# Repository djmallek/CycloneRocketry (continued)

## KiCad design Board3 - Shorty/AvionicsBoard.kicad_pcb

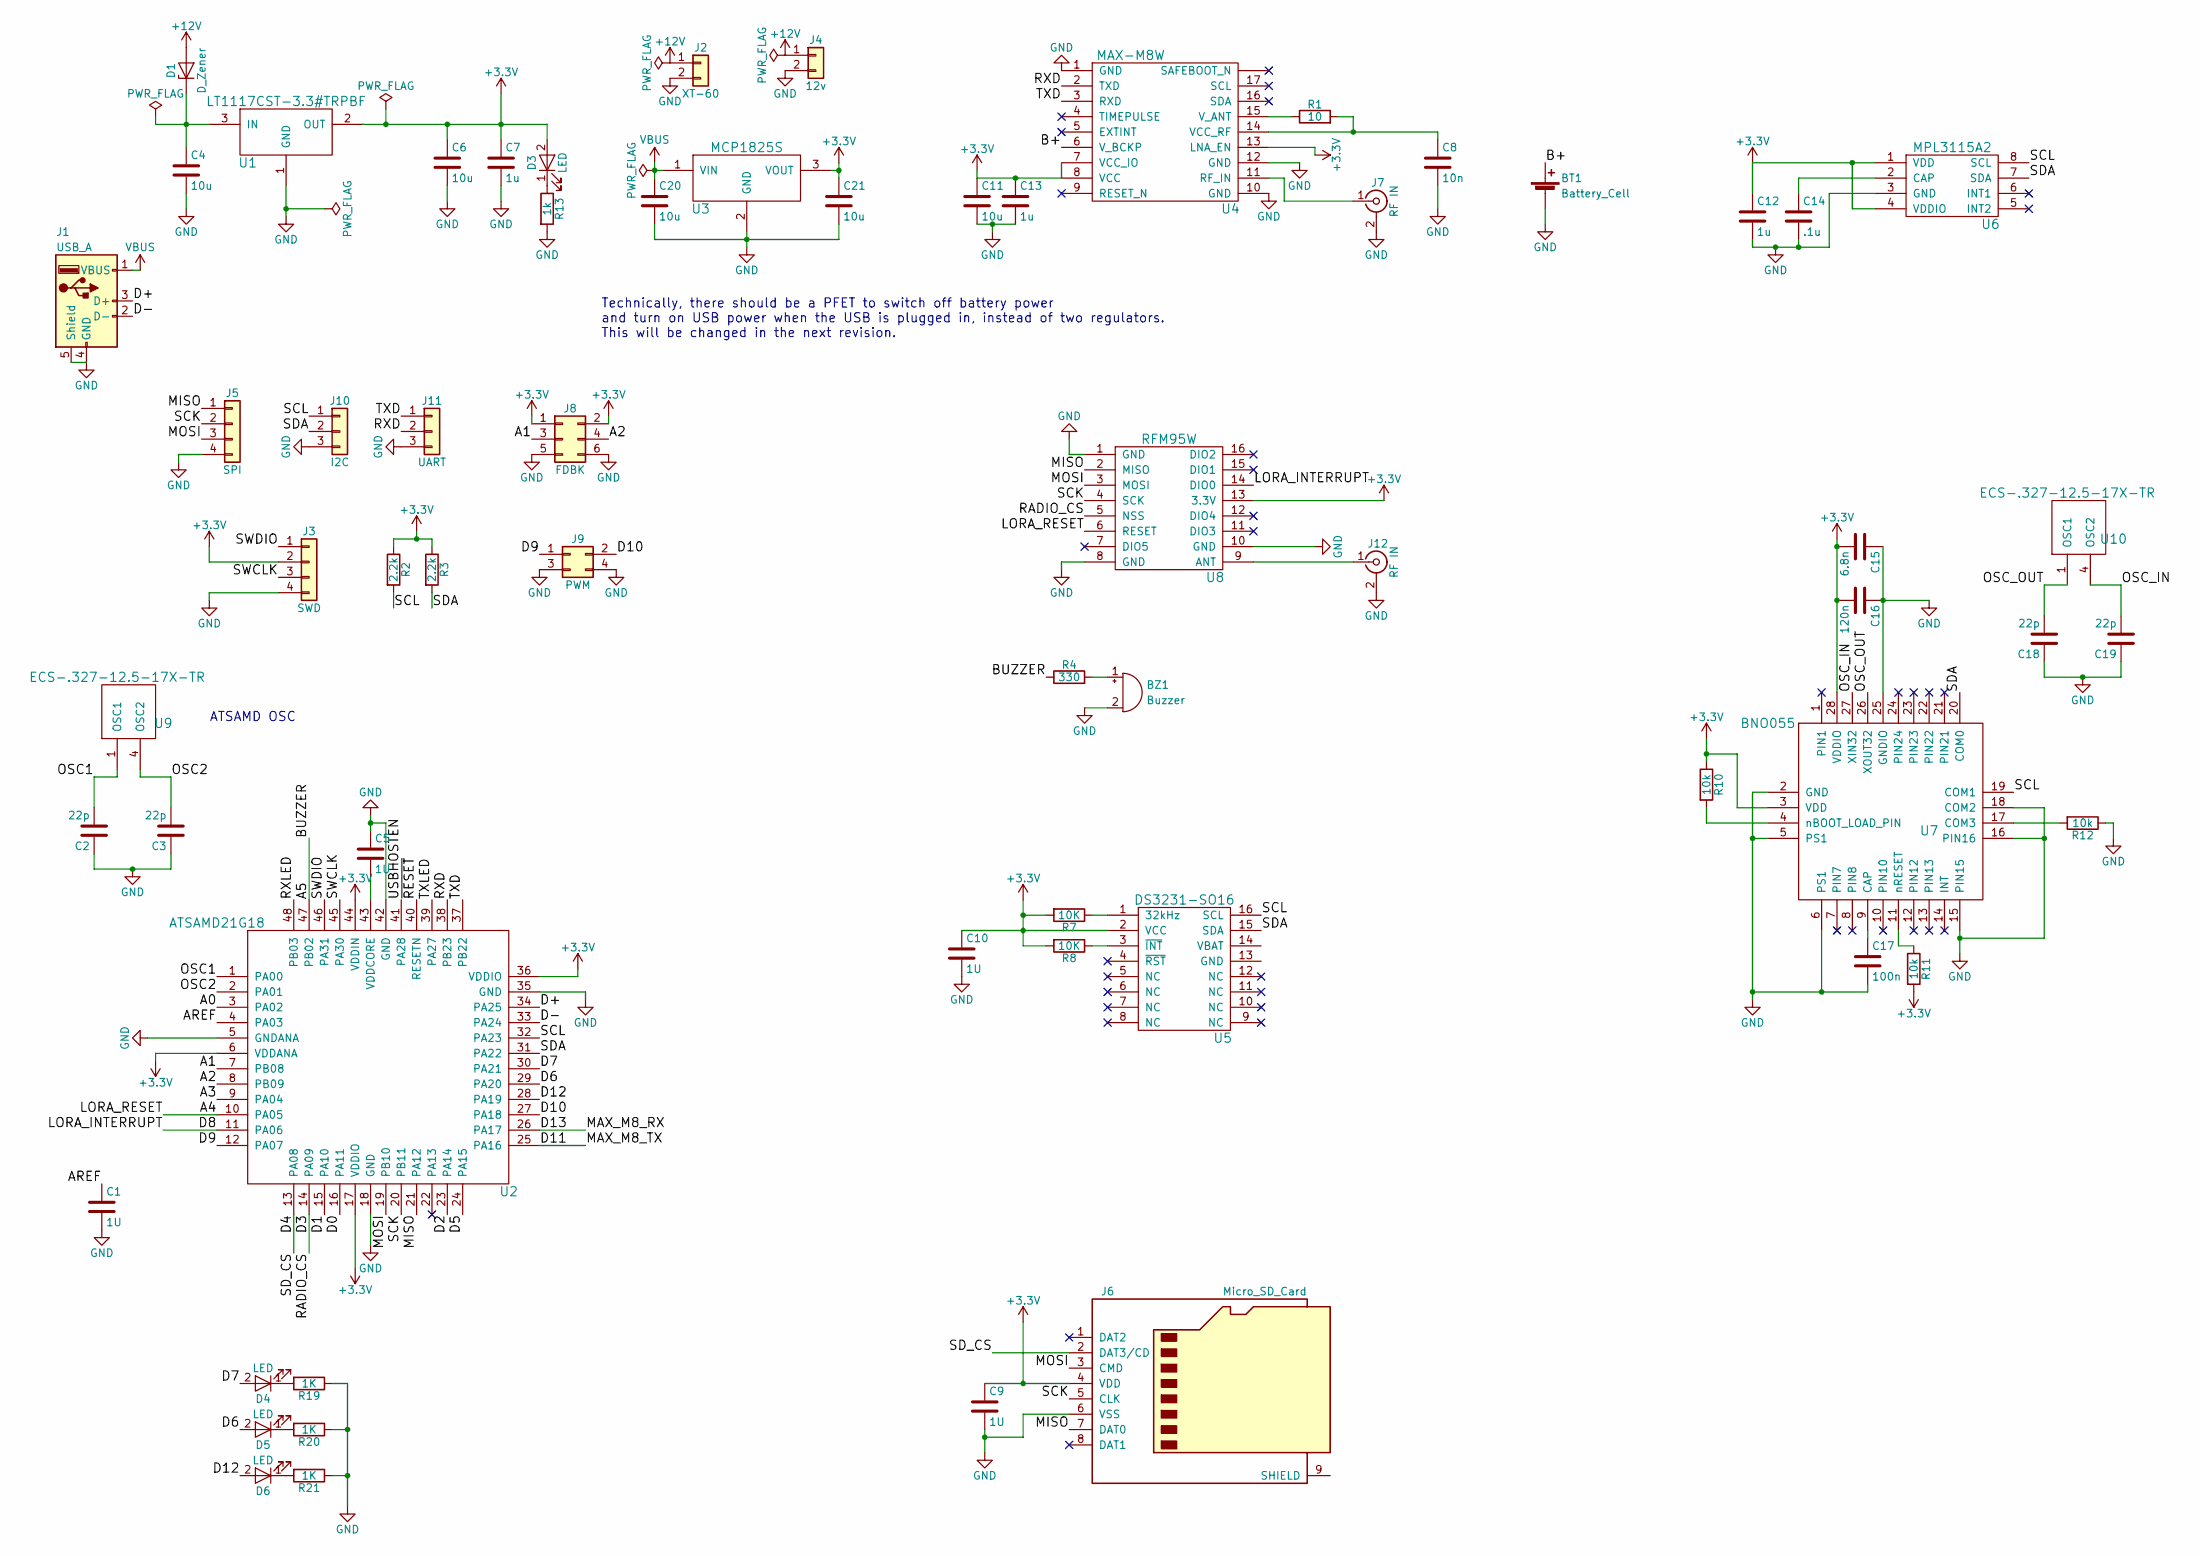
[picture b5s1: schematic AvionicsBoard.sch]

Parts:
BT1: Battery_Cell; BR-1225A_HB
BZ1: Buzzer; CUI_CMT-5023S-SMT
C1, C5, C9, C10: 1U; C_0805
C2, C3, C18, C19: 22p; C_0805
C4, C6, C11, C20, C21: 10u; C_1206
C7, C12, C13: 1u; C_0805
C8: 10n; C_0805
C14: .1u; C_0805
C15: 6.8n; C_1206
C16: 120n; C_1206
C17: 100n; C_0805
D1: D_Zener; D_SOD-123
D3, D4, D5, D6: LED; LED_1206
J1: USB_A; USB_Mini-B
J2: XT-60; XT60
J3: SWD; Pin_Header_Straight_1x04_Pitch2.54mm
J4: 12v; Pin_Header_Straight_1x02_Pitch2.54mm
J5: SPI; Pin_Header_Straight_1x04_Pitch2.54mm
J6: Micro_SD_Card; microSD_Card_Receptacle_Wuerth_693072010801
J7, J12: RF IN; SMA_TH
J8: FDBK; Pin_Header_Straight_2x03_Pitch2.54mm
J9: PWM; Pin_Header_Straight_2x02_Pitch2.54mm
J10: I2C; Pin_Header_Straight_1x03_Pitch2.54mm
J11: UART; Pin_Header_Straight_1x03_Pitch2.54mm
R1: 10; R_0805
R2, R3: 2.2k; R_0805
R4: 330; R_0805
R7, R8: 10K; R_0805
R10, R11, R12: 10k; R_0805
R13: 1k; R_0805
R19, R20, R21: 1K; R_0805
U1: LT1117CST-3.3#TRPBF; SOT-223-3_TabPin2
U2: ATSAMD21G18; TQFP-48_7x7mm_Pitch0.5mm
U3: MCP1825S; SOT-223-3_TabPin2
U4: MAX-M8W; MAX_M82
U5: DS3231-SO16; SOIC-16W_7.5x10.3mm_Pitch1.27mm
U6: MPL3115A2
U7: BNO055; BNO055-LGA
U8: RFM95W
U9, U10: ECS-.327-12.5-17X-TR; XC1195CT-ND

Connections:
+3V3: C6.1, C7.1, C9.1, C10.1, C11.1, C12.1, C13.1, C15.2, C16.2, C21.1, D3.2 (A), J3.2, J6.4 (VDD), J8.1, J8.2, R2.1, R3.1, R7.2, R8.2, R10.1, R11.2, U1.2 (OUT), U2.6 (VDDANA), U2.17 (VDDIO), U2.36 (VDDIO), U2.44 (VDDIN), U3.3 (VOUT), U4.7 (VCC_IO), U4.8 (VCC), U4.13 (LNA_EN), U5.2 (VCC), U6.1 (VDD), U6.4 (VDDIO), U7.3 (VDD), U7.28 (VDDIO), U8.13 (3.3V); also elsewhere on the board
+12V: D1.2 (A), J2.1, J4.1
/A0: U2.3 (PA02)
/A1: J8.3, U2.7 (PB08)
/A2: J8.4, U2.8 (PB09)
/A3: U2.9 (PA04)
/A4: U2.10 (PA05), U8.6 (RESET)
/A5: R4.1, U2.47 (PB02)
/AREF: C1.1, U2.4 (PA03)
/B+: BT1.1 (+), U4.6 (V_BCKP)
/D0: U2.16 (PA11)
/D1: U2.15 (PA10)
/D2: U2.23 (PA14)
/D3: U2.14 (PA09), U8.5 (NSS)
/D4: J6.2 (DAT3/CD), U2.13 (PA08); also elsewhere on the board
/D5: U2.24 (PA15)
/D6: D5.2 (A), U2.29 (PA20)
/D7: D4.2 (A), U2.30 (PA21); also elsewhere on the board
/D8: U2.11 (PA06), U8.14 (DIO0)
/D9: J9.1, U2.12 (PA07)
/D10: J9.2, U2.27 (PA18)
/D11: U2.25 (PA16)
/D12: D6.2 (A), U2.28 (PA19)
/D13: U2.26 (PA17)
/D+: J1.3 (D+), U2.34 (PA25)
/D-: J1.2 (D-), U2.33 (PA24)
/MISO: J5.1, J6.7 (DAT0), U2.21 (PA12), U8.2 (MISO)
/MOSI: J5.3, J6.3 (CMD), U2.19 (PB10), U8.3 (MOSI)
/OSC1: C2.2, U2.1 (PA00), U9.1 (OSC1)
/OSC2: C3.2, U2.2 (PA01), U9.4 (OSC2)
/OSC_IN: C19.2, U7.27 (XIN32), U10.4 (OSC2)
/OSC_OUT: C18.2, U7.26 (XOUT32), U10.1 (OSC1)
/RXD: J11.2, U2.38 (PB23), U4.2 (TXD)
/RXLED: U2.48 (PB03)
/SCK: J5.2, J6.5 (CLK), U2.20 (PB11), U8.4 (SCK)
/SCL: J10.1, R2.2, U2.32 (PA23), U5.16 (SCL), U6.8 (SCL), U7.19 (COM1)
/SDA: J10.2, R3.2, U2.31 (PA22), U5.15 (SDA), U6.7 (SDA), U7.20 (COM0)
/SWCLK: J3.3, U2.45 (PA30)
/SWDIO: J3.1, U2.46 (PA31)
/TXD: J11.1, U2.37 (PB22), U4.3 (RXD)
/TXLED: U2.39 (PA27)
/USBHOSTEN: U2.41 (PA28)
/~RESET: U2.40 (RESETN)
GND: BT1.2 (-), BZ1.2 (+), C1.2, C2.1, C3.1, C4.2, C5.1, C6.2, C7.2, C8.2, C9.2, C10.2, C11.2, C12.2, C13.2, C14.2, C15.1, C16.1, C17.2, C18.1, C19.1, C20.2, C21.2, J1.4 (GND), J1.5 (Shield), J2.2, J3.4, J4.2, J5.4, J6.6 (VSS), J6.9 (SHIELD), J7.2 (Ext), J8.5, J8.6, J9.3, J9.4, J10.3, J11.3, J12.2 (Ext), R12.1, R13.2, R19.1, R20.1, R21.1, U1.1 (GND), U2.5 (GNDANA), U2.18 (GND), U2.35 (GND), U2.42 (GND), U3.2 (GND), U4.1 (GND), U4.10 (GND), U4.12 (GND), U5.13 (GND), U6.3 (GND), U7.2 (GND), U7.5 (PS1), U7.6 (PS1), U7.15 (PIN15), U7.16 (PIN16), U7.18 (COM2), U7.25 (GNDIO), U8.1 (GND), U8.8 (GND), U8.10 (GND); also elsewhere on the board
unnamed: BZ1.1 (-), R4.2
unnamed: C4.1, D1.1 (K), U1.3 (IN)
unnamed: C5.2, U2.43 (VDDCORE)
unnamed: C8.1, R1.2, U4.14 (VCC_RF)
unnamed: C14.1, U6.2 (CAP)
unnamed: C17.1, U7.9 (CAP)
unnamed: D3.1 (K), R13.1
unnamed: D4.1 (K), R19.2
unnamed: D5.1 (K), R20.2
unnamed: D6.1 (K), R21.2
unnamed: J7.1 (In), U4.11 (RF_IN)
unnamed: J12.1 (In), U8.9 (ANT)
unnamed: R1.1, U4.15 (V_ANT)
unnamed: R7.1, U5.1 (32kHz)
unnamed: R8.1, U5.3 (~INT)
unnamed: R10.2, U7.4 (nBOOT_LOAD_PIN)
unnamed: R11.1, U7.11 (nRESET)
unnamed: R12.2, U7.17 (COM3)
VBUS: C20.1, J1.1 (VBUS), U3.1 (VIN)

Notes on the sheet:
ATSAMD OSC
Technically, there should be a PFET to switch off battery power and turn on USB power when the USB is plugged in, instead of two regulators. This will be changed in the next revision.

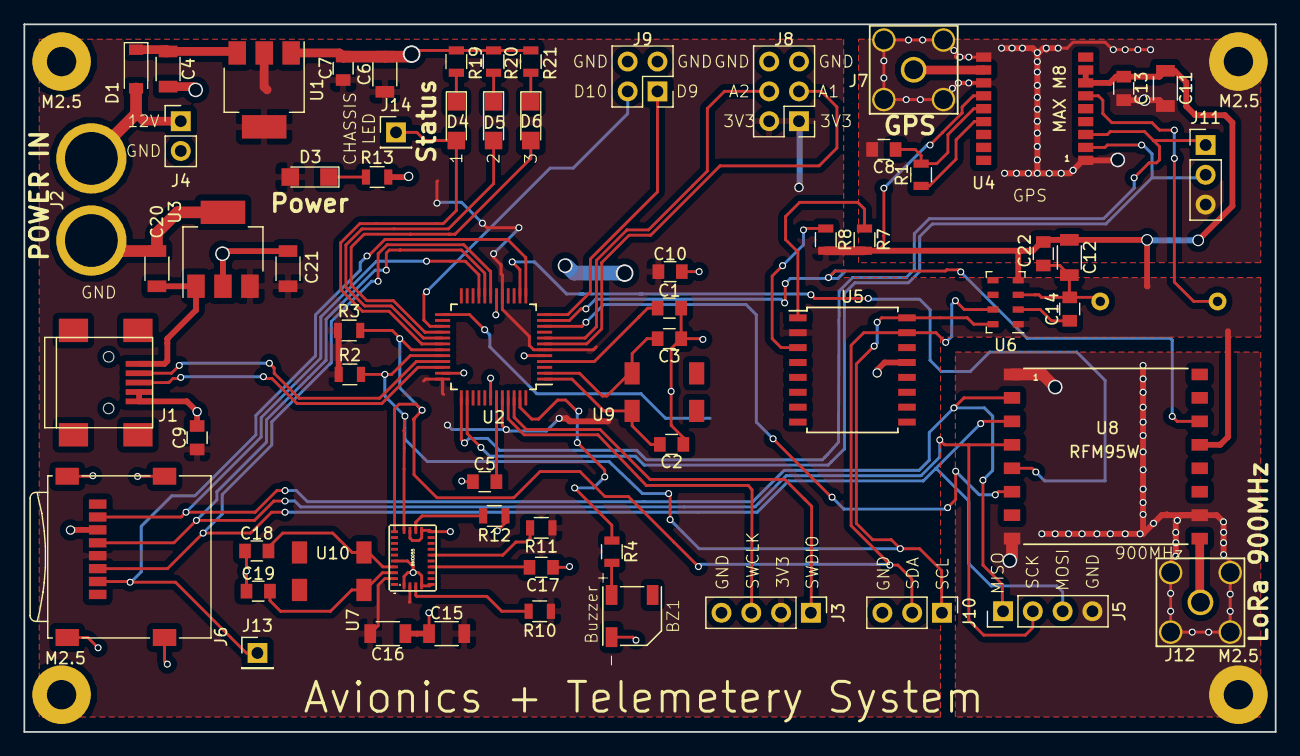
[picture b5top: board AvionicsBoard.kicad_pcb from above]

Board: 2 copper layers, 106.7 x 60.3 mm, 70 parts (1 on the bottom side), 51 nets.

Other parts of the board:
C22: 100n; C_0805
J13: SD_CS; Pin_Header_Straight_1x01_Pitch2.54mm
J14: CHASSIS LED; Pin_Header_Straight_1x01_Pitch2.54mm
J15, J16, J17, J18: CHASSIS GND; MountingHole_2.5mm_Pad

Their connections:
+3V3: C22.1; also elsewhere on the board
/D4: J13.1; also elsewhere on the board
/D7: J14.1; also elsewhere on the board
GND: C22.2, J15.1, J16.1, J17.1, J18.1; also elsewhere on the board

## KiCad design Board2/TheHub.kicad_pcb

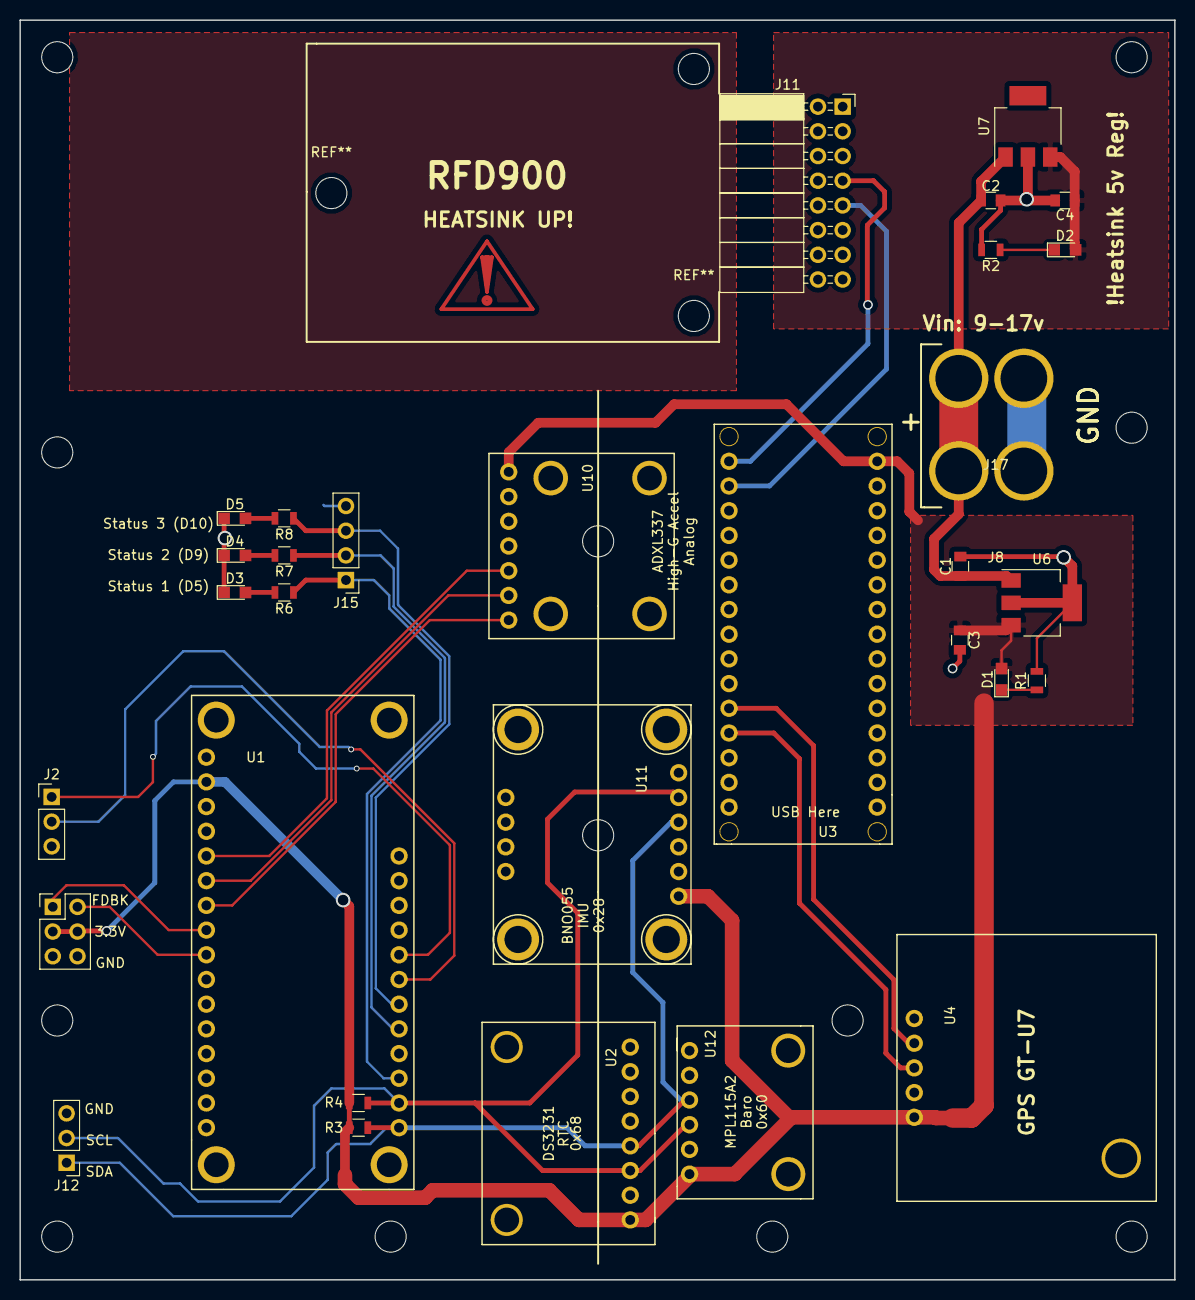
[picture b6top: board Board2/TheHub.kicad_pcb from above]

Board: 2 copper layers, 118.7 x 129.5 mm, 32 parts (0 on the bottom side), 25 nets.

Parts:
C1, C2, C3, C4: 10U; C_0805
D1, D2, D3, D4, D5: LED; LED_0805
J1: Actuator Fdbk Conn; Pin_Header_Straight_2x03_Pitch2.54mm
J2: Conn_01x03; Pin_Header_Straight_1x03_Pitch2.54mm
J8: 12V MAIN POWER; XT60
J11: RFD900; Socket_Strip_Angled_2x08_Pitch2.54mm
J12: I2C_1 Test Point; Pin_Header_Straight_1x03_Pitch2.54mm
J15: GPIO Test; Pin_Header_Straight_1x04_Pitch2.54mm
J17: 12V OUT; XT60
R1, R2: 220; R_0805
R3, R4: 2.2K; R_0805
R6, R7, R8: 1k; R_0805
U1: FeatherM0
U2: DS3231
U3: ArduinoNano
U4: GT-U7_GPS
U6: TL1963; SOT-223-3Lead_TabPin2
U7: LM340MP-5.0; SOT-223
U10: ADXL377
U11: BNO055
U12: MPL115A2

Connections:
+3V3: C3.1, D1.2, J1.3, J1.4, R3.1, R4.1, U1.2, U2.1, U3.15, U4.5, U6.3, U10.1, U11.1, U12.6
+5V: C4.1, D2.2, J11.4, U7.3
+12V: C1.1, C2.1, J8.1, J17.1, U6.1, U7.1
/A0: U1.5, U10.5
/A1: U1.6, U10.6
/A2: U1.7, U10.7
/A_FDBK_0: J1.1, U1.8
/A_FDBK_1: J1.2, U1.9
/ActuatorDir: J2.1, U1.24
/ActuatorPWM: J2.2, U1.23
/GPS_RX: U3.27, U4.3
/GPS_TX: U3.26, U4.2
/RFD900_RX: J11.7, U3.16
/RFD900_TX: J11.9, U3.17
/SCL_1: J12.2, R4.2, U1.18, U2.3, U11.5, U12.4
/SDA_1: J12.1, R3.2, U1.17, U2.4, U11.4, U12.3
/Status1: J15.1, R6.1, U1.19
/Status2: J15.2, R7.1, U1.21
/Status3: J15.3, R8.1, U1.22
GND: C1.2, C2.2, C3.2, C4.2, D3.1, D4.1, D5.1, J1.5, J1.6, J2.3, J8.2, J11.1, J11.2, J11.16, J12.3, J15.4, J17.2, R1.2, R2.2, U1.4, U1.16, U2.2, U3.14, U3.19, U4.4, U6.2, U7.2, U10.3, U11.3, U12.5
unnamed: D1.1, R1.1
unnamed: D2.1, R2.1
unnamed: D3.2, R6.2
unnamed: D4.2, R7.2
unnamed: D5.2, R8.2

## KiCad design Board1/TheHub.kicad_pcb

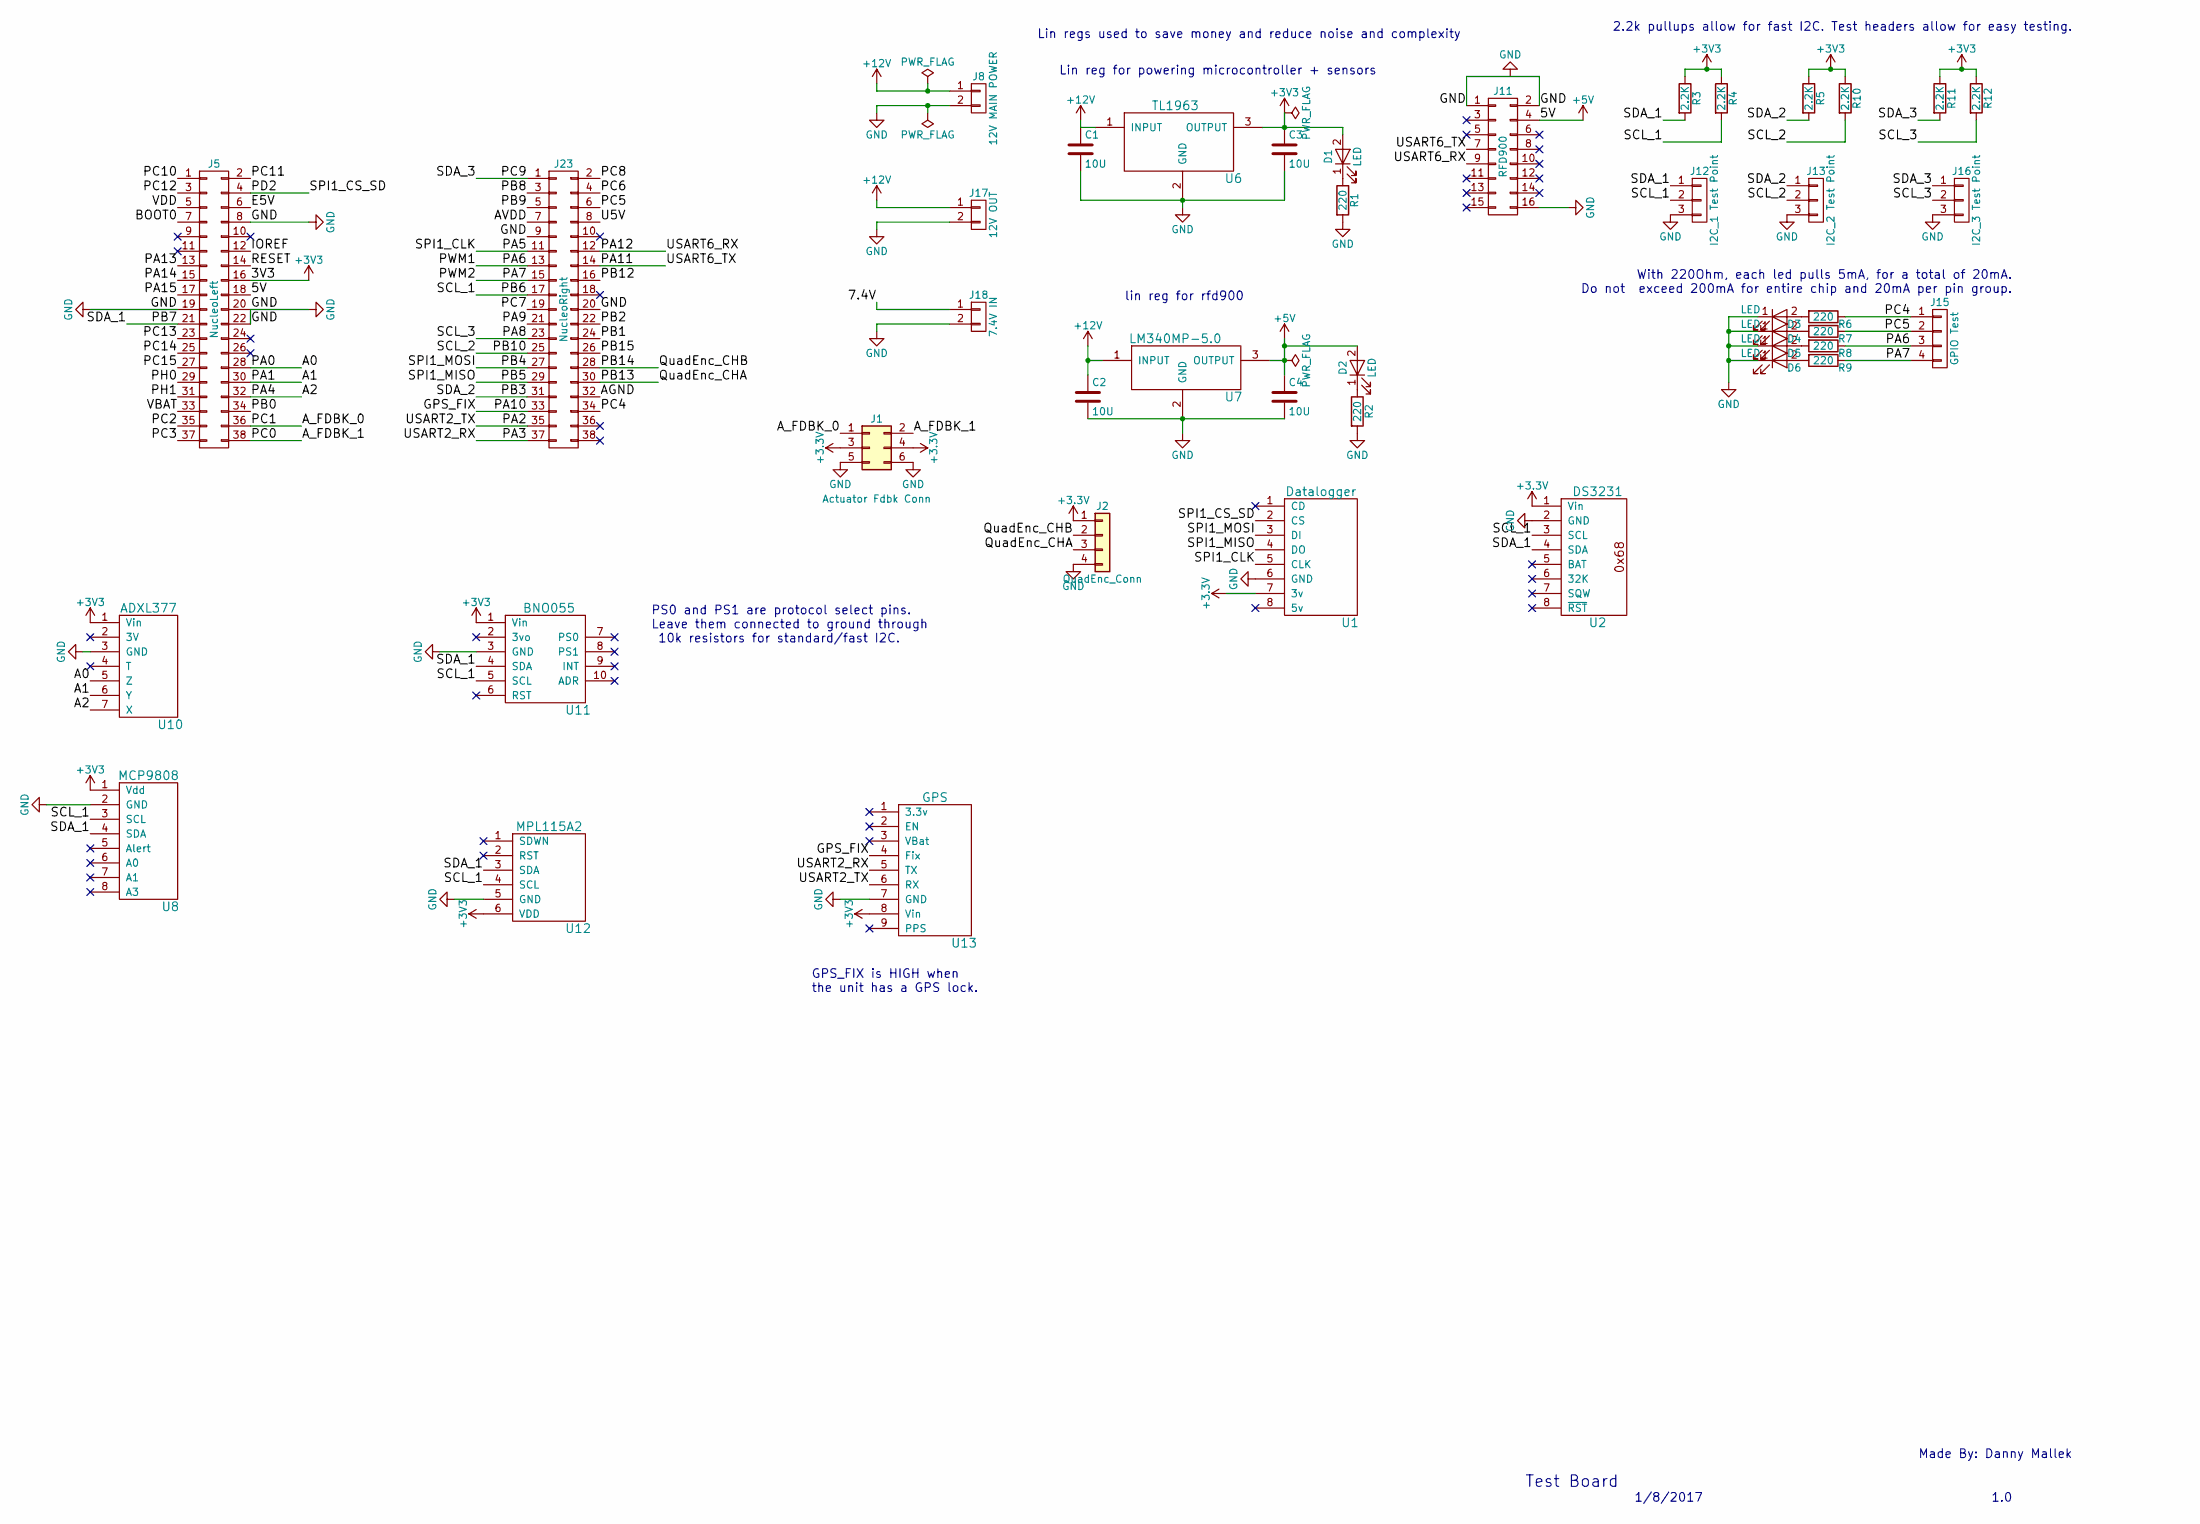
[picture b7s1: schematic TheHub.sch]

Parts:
C1, C2, C3, C4: 10U; C_0805
D1, D2, D3, D4, D5, D6: LED; LED_0805
J1: Actuator Fdbk Conn; Pin_Header_Straight_2x03_Pitch2.54mm
J2: QuadEnc_Conn; Pin_Header_Straight_1x04_Pitch2.54mm
J5: NucleoLeft; Socket_Strip_Straight_2x19_Pitch2.54mm
J8: 12V MAIN POWER; XT60
J11: RFD900; Socket_Strip_Angled_2x08_Pitch2.54mm
J12: I2C_1 Test Point; Pin_Header_Straight_1x03_Pitch2.54mm
J13: I2C_2 Test Point; Pin_Header_Straight_1x03_Pitch2.54mm
J15: GPIO Test; Pin_Header_Straight_1x04_Pitch2.54mm
J16: I2C_3 Test Point; Pin_Header_Straight_1x03_Pitch2.54mm
J17: 12V OUT; XT60
J18: 7.4V IN; XT60
J23: NucleoRight; Socket_Strip_Straight_2x19_Pitch2.54mm
R1, R2, R6, R7, R8, R9: 220; R_0805
R3, R4, R5, R10, R11, R12: 2.2K; R_0805
U1: Datalogger
U2: DS3231
U6: TL1963; SOT-223-3Lead_TabPin2
U7: LM340MP-5.0; SOT-223-3Lead_TabPin2
U8: MCP9808
U10: ADXL377
U11: BNO055
U12: MPL115A2
U13: GPS; Adafruit_GPS

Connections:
+5V: C4.1, D2.2 (A), J5.18, J11.4, U7.3 (OUTPUT)
+12V: C1.1, C2.1, J8.1, J17.1, U6.1 (INPUT), U7.1 (INPUT)
/A0: J5.28, U10.5 (Z)
/A1: J5.30, U10.6 (Y)
/A2: J5.32, U10.7 (X)
/AGND: J23.32
/AVDD: J23.7
/A_FDBK_0: J1.1, J5.36
/A_FDBK_1: J1.2, J5.38
/BOOT0: J5.7
/E5V: J5.6
/GPS_FIX: J23.33, U13.4 (Fix)
/IOREF: J5.12
/PA2: J23.35, U13.6 (RX)
/PA3: J23.37, U13.5 (TX)
/PA5: J23.11, U1.5 (CLK)
/PA6: J15.3, J23.13, R8.1
/PA7: J15.4, J23.15, R9.1
/PA8: J16.2, J23.23, R12.2
/PA9: J23.21
/PA11: J11.7, J23.14
/PA12: J11.9, J23.12
/PA13: J5.13
/PA14: J5.15
/PA15: J5.17
/PB0: J5.34
/PB1: J23.24
/PB2: J23.22
/PB3: J13.1, J23.31, R5.2
/PB4: J23.27, U1.3 (DI)
/PB5: J23.29, U1.4 (DO)
/PB6: J12.2, J23.17, R4.2, U2.3 (SCL), U8.3 (SCL), U11.5 (SCL), U12.4 (SCL)
/PB7: J5.21, J12.1, R3.2, U2.4 (SDA), U8.4 (SDA), U11.4 (SDA), U12.3 (SDA)
/PB8: J23.3
/PB9: J23.5
/PB10: J13.2, J23.25, R10.2
/PB12: J23.16
/PB13: J2.3, J23.30
/PB14: J2.2, J23.28
/PB15: J23.26
/PC2: J5.35
/PC3: J5.37
/PC4: J15.1, J23.34, R6.1
/PC5: J15.2, J23.6, R7.1
/PC6: J23.4
/PC7: J23.19
/PC8: J23.2
/PC9: J16.1, J23.1, R11.2
/PC10: J5.1
/PC11: J5.2
/PC12: J5.3
/PC13: J5.23
/PC14: J5.25
/PC15: J5.27
/PD2: J5.4, U1.2 (CS)
/PH0: J5.29
/PH1: J5.31
/RESET: J5.14
/U5V: J23.8
/VBAT: J5.33
/VDD: J5.5
GND: C1.2, C2.2, C3.2, C4.2, D3.1 (K), D4.1 (K), D5.1 (K), D6.1 (K), J1.5, J1.6, J2.4, J5.8, J5.19, J5.20, J5.22, J8.2, J11.1, J11.2, J11.16, J12.3, J13.3, J16.3, J17.2, J18.2, J23.9, J23.20, R1.2, R2.2, U1.6 (GND), U2.2 (GND), U6.2 (GND), U7.2 (GND), U8.2 (GND), U10.3 (GND), U11.3 (GND), U12.5 (GND), U13.7 (GND)
unnamed: D1.1 (K), R1.1
unnamed: D2.1 (K), R2.1
unnamed: D3.2 (A), R6.2
unnamed: D4.2 (A), R7.2
unnamed: D5.2 (A), R8.2
unnamed: D6.2 (A), R9.2

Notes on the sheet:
With 220Ohm, each led pulls 5mA, for a total of 20mA. Do not exceed 200mA for entire chip and 20mA per pin group.
PS0 and PS1 are protocol select pins. Leave them connected to ground through 10k resistors for standard/fast I2C.
GPS_FIX is HIGH when the unit has a GPS lock.
Test Board
1.0
1/8/2017
Made By: Danny Mallek
2.2k pullups allow for fast I2C. Test headers allow for easy testing.
Lin reg for powering microcontroller + sensors
lin reg for rfd900
Lin regs used to save money and reduce noise and complexity

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
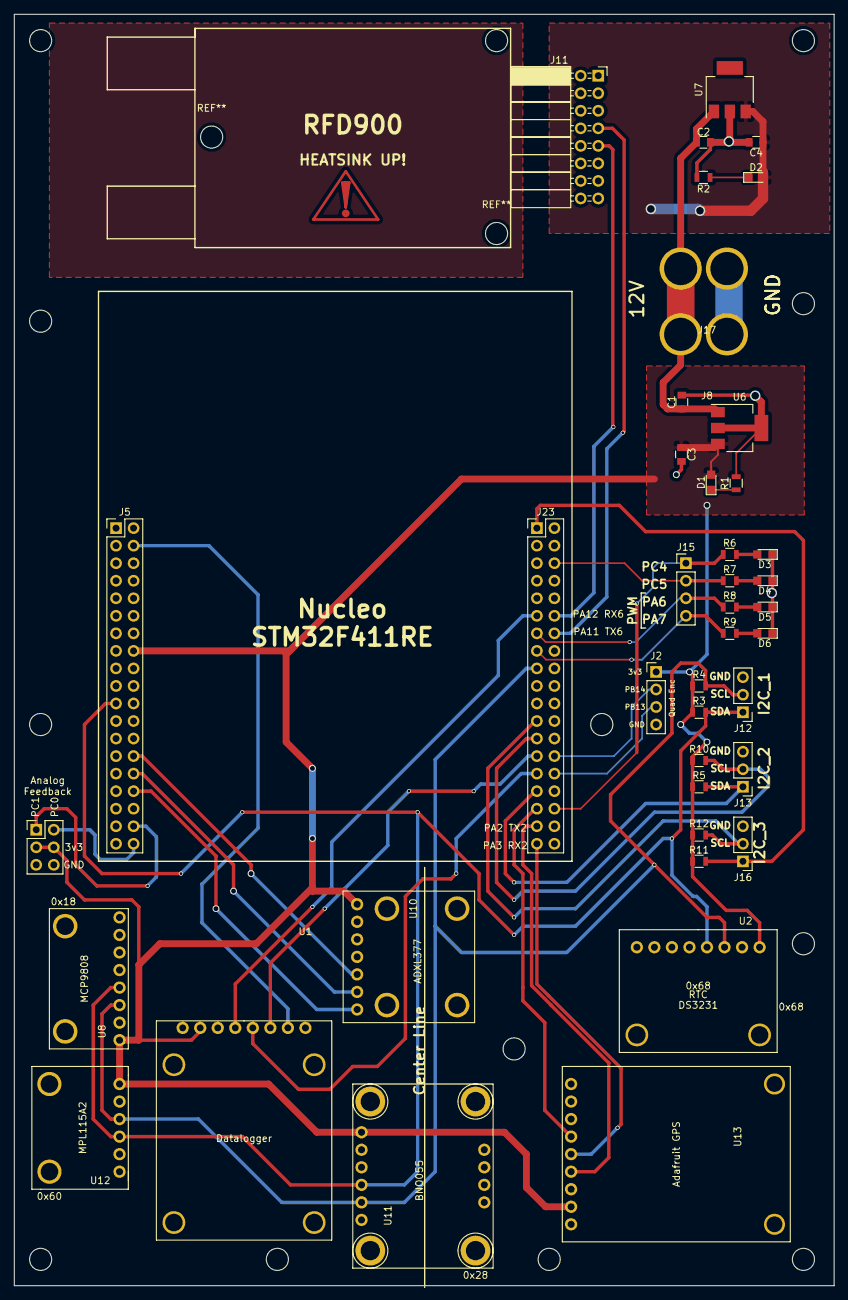
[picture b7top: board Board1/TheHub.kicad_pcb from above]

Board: 2 copper layers, 118.7 x 184.1 mm, 42 parts (0 on the bottom side), 36 nets.

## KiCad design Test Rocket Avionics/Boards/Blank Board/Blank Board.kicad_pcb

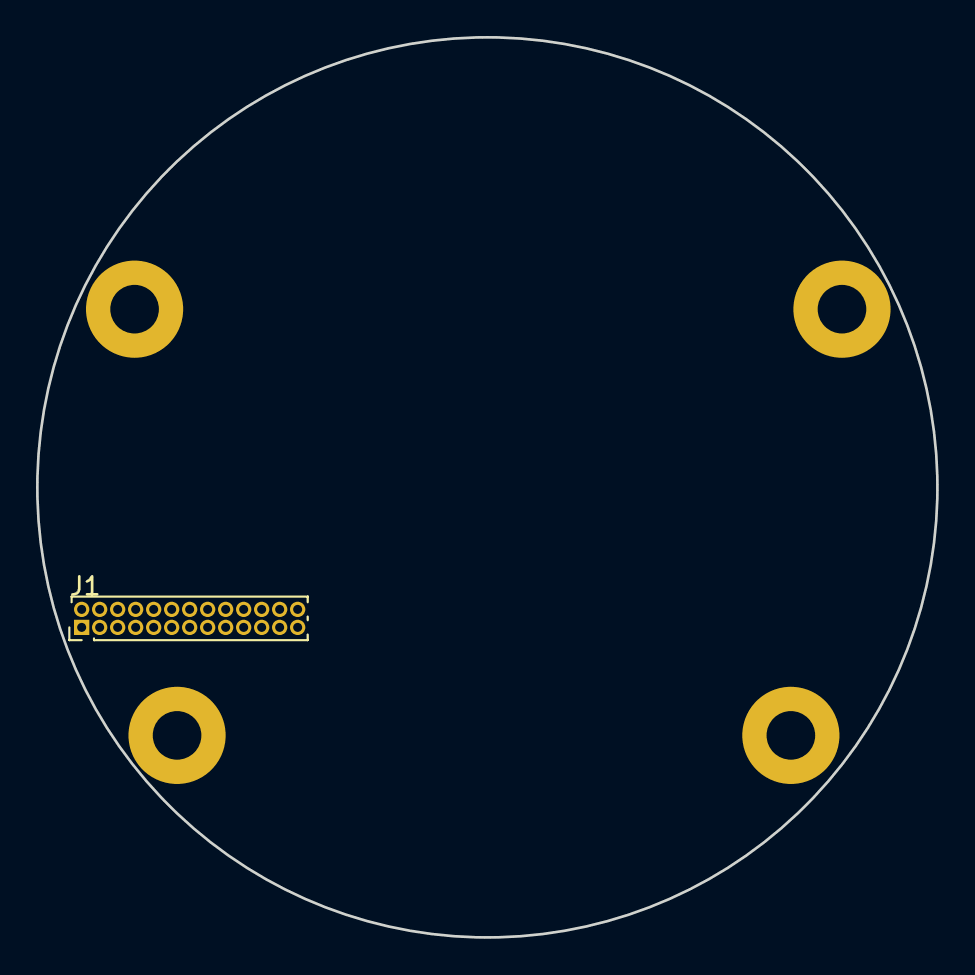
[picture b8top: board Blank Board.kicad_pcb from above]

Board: 4 copper layers, 50.0 x 50.0 mm, 5 parts (0 on the bottom side), 2 nets.

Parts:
J1: EXPANSION_HEADER; Pin_Header_Straight_2x13_Pitch1.00mm
J10, J11, J12, J13: CHASSIS_GND; MountingHole_2.7mm_M2.5_Pad

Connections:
+3V3: J1.9, J1.11
GND: J1.7, J1.8, J1.13, J1.15, J1.17, J10.1, J11.1, J12.1, J13.1

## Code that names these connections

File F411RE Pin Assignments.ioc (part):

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Mcu.Name=STM32F411R(C-E)Tx
Mcu.Package=LQFP64
Mcu.UserName=STM32F411RETx
PA0-WKUP.Signal=ADCx_IN0
PA1.Signal=ADCx_IN1
PA10.Signal=GPIO_Input
PA11.Mode=Asynchronous
PA11.Signal=USART6_TX
PA12.Mode=Asynchronous
PA12.Signal=USART6_RX
PA2.Mode=Asynchronous
PA2.Signal=USART2_TX
PA3.Mode=Asynchronous
PA3.Signal=USART2_RX
PA4.Signal=ADCx_IN4
PA5.Mode=Full_Duplex_Master
PA5.Signal=SPI1_SCK
PA6.Signal=S_TIM3_CH1
PA7.Signal=S_TIM3_CH2
PA8.Mode=I2C
PA8.Signal=I2C3_SCL
PB10.Mode=I2C
PB10.Signal=I2C2_SCL
PB13.GPIOParameters=GPIO_Label
PB13.GPIO_Label=Quad Encoder ChA
PB13.Signal=GPIO_Input
PB14.GPIOParameters=GPIO_Label
PB14.GPIO_Label=Quad Encoder ChB
PB14.Signal=GPIO_Input
PB3.Mode=I2C
PB3.Signal=I2C2_SDA
PB4.Mode=Full_Duplex_Master
PB4.Signal=SPI1_MISO
PB5.Mode=Full_Duplex_Master
PB5.Signal=SPI1_MOSI
PB6.Mode=I2C
PB6.Signal=I2C1_SCL
PB7.Mode=I2C
PB7.Signal=I2C1_SDA
PC0.Signal=ADCx_IN10
PC1.Signal=ADCx_IN11
PC9.Mode=I2C
PC9.Signal=I2C3_SDA
PD2.GPIOParameters=GPIO_Label
PD2.GPIO_Label=ChipSelect SD
PD2.Signal=GPIO_Output
RCC.HSE_VALUE=25000000
RCC.SYSCLKFreq_VALUE=16000000

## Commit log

2018-01-05 Copy work from "The Hub"
    The Hub is a board that is used for quickly prototyping and testing software meant for the final board revision. It is easier to make modifications to and has a higher success rate than custom PCBs.
2018-01-05 Add ADXL377 schematic part
2018-01-06 Add schematic library for BNO055, MCP9808, and MPL115A2
    Just the schematics, NOT the footprints yet
2018-01-06 Add GPS schematic
2018-01-06 Add pin assignments for 2xPWM, I2C 1-3, UART2, UART6, and ADC 0-2
    Pin assignments can be viewed in STMCube MX from the .ioc file
2018-01-07 Add note or BNO055, add GPS, add nucleo pin declaration for GPS_FIX GPIO_Input
2018-01-07 Annotate schematic
2018-01-07 Create Adafruit_GPS footprint
2018-01-07 Create BNO055 footprint
2018-01-07 Update ADXL377 schematic: change index to 1, Update BNO055 to have larger mounting hole pad
2018-01-07 Create MCP9808 footprint
2018-01-07 Create ADXL377 footprint
2018-01-08 Add MPL115A2 footprint, annotate schematic
2018-01-08 Associate parts using CvPCB
2018-01-08 Generate netlist
2018-01-08 Initialize the PCB
2018-01-08 Make PCB have smaller profile
2018-01-08 Created center line and aligned gyro and accelerometers
2018-01-08 Route all signal and power traces
2018-01-08 Add offset to 3D model on nucleo pins so that they display correctly
2018-01-08 Align hole mounts
2018-01-08 Add logo to the board
2018-01-08 Add labeling text for probe points
2018-01-10 Add proper mounting holes for MPL115A2, increase drill by 0.01mm on MCP9808
2018-01-10 Update XT60 connectors, replae old XT60 footprint on board, generate new gerbers
2018-01-10 Update MPL115A2 on pcb to current footprint
2018-01-11 Add mounting points for RFD900
2018-01-22 Add to schematic and CubeMX: IO for SD card datalogger, 2x analog pot inputs, quad encoder
2018-01-22 Add Datalogger library schematic and integrate into schematic
2018-01-22 Eat dinner, create footprint for Datalogger
2018-01-22 Add DS3231 to schematic lib, integrate DS3231 into schematic
2018-01-22 Add DS3231 footprint
2018-01-22 Associate schematic with footprints
2018-01-22 Update netlist to use staight headars instead of angled
2018-01-22 Add Datalogger and RTC to PCB, add I2C addresses to silkscreen
2018-01-22 Add silkscreen lables for RX, TX, Nucleo, and analog feedback
2018-01-25 Add BOM
2018-01-25 Updated BOM
2018-01-25 Update BOM
2018-04-19 Create new schematic for Feather M0
    Copied form th Nucleo Hub, add Nano and Feather M0 schematics
2018-04-19 Create footprint for Feather M0, correct schematic changes
2018-04-19 Create Arduino Nano footprint
2018-04-19 Associate parts and generate netlist
2018-04-19 Remove previous components from the board
2018-04-19 Relayout Hub 2 Board
2018-04-19 Add nice text markings
2018-04-20 Modify RFD footprint, generate Gerbs
2018-06-12 Add most of the schematic fo the new board
2018-06-12 Associate some arts, make some schematic changes
2018-06-13 create more footprints, associate parts
2018-06-13 Start general layout
2018-06-17 Finished routing board, added logo
2018-07-04 Fix BNO055 footprint and board layout
2018-09-23 Generatin those gerbs
2018-09-23 Add presentation
2018-10-31 Change CS for SD card to PA08 (aka pin 13), Add RDF900 Serial ports, Add 0 ohm GPS selectors, add GT-07 GPS, add 5v regualtor for RFD900
2018-11-01 Little bit o PCB layout
2018-11-02 Get that RFD900 UART outta the uC to that radio
2018-11-03 Make board that is too fat
2018-11-03 Create skinny boi
2018-11-03 Add LEDs, cleanup traces
2018-11-03 Added finshing touches to board. Investigate GPS and RFM95 RF paths!! RFD900 mounting hole sneed resizing!!
2018-11-03 Doen
2018-11-03 Add solidworks chassis
    cleanup folders later
2018-11-03 Add Avionics Cost Document
2018-12-09 Layout
2018-12-10 Finishing touches on RF
2018-12-10 Do some board cleanup, generate gerbs
2019-01-06 Add buzzer, LorA interrupt and reset lines, fix issue with USB and battery power, reduce RF path lengths, add better microstrip matching for LoRa and GPS, create ALLPCB BOM
2019-01-06 Generate Gerbers
2019-01-06 Update cost option 4
2019-01-06 Add Cyclone Rocketry Logo, generate gerbers
2019-01-19 dsfafdsa
2019-02-02 Create Circular Avionics Board
2019-02-02 Add RF Circular Board Schematic
2019-02-23 Create 50mm Circular board
2019-02-23 Update some stuff
2019-02-23 Get too involved
2019-03-24 Connect JST connector to VBatt+ and GND nets
2019-04-03 Remove DS3231
2019-04-03 Remove DS3231 and expand the J3 connector to include USB and improve pin ordering. Various bug fixes
2019-04-03 Create Blank Board, Start RF Board
2019-04-03 Mostly create RF Board
2019-04-08 Create the Hub 2, a smaller version of the original hub that will fit inside a rocket
2019-04-08 Add BOM and GERBs
2019-04-09 For Hub2: add servo2 and GPS changed to breakout for MAX M8Q
2019-05-01 Add micro SD Card, clean up ref des, power 6v boost directly from battery instead of 3.3V rail
2019-05-01 Add LMS303C and BMP280
2019-05-01 Create Gerbers, move SD card up for more error margin
